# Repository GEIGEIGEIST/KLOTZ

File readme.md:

<picture>
  <source media="(prefers-color-scheme: dark)" srcset="/docs/images/KLOTZ_font_dark.svg">
  <source media="(prefers-color-scheme: light)" srcset="/docs/images/KLOTZ_font_bright.svg">
  
</picture>

# KLOTZ SPLIT KEYBOARD

KLOTZ is a 34 key column-staggered choc split keyboard running [ZMK](https://zmk.dev/). It supports a low profile encoder, three status LEDs on every side and the SplitKB tenting puck.

## LAYOUT

## PCB

[Here](/PCB/) you can find the KiCad files and Gerbers for the KLOTZ.

## SWITCHPLATE

And [here](/switchplate/) is the switchplate, which you should use, if you plan to use hotswap sockets.

## KNOB

You can use pretty much any knob, which works with EC12 encoder, but [here](/knob/) you can find one, I designed for the KLOTZ.

## BUILD GUIDE

The build guide for the KLOTZ can be found [here](/docs/buildguide.md).

## FIRMWARE

[ZMK config](https://github.com/GEIGEIGEIST/zmk-config-klotz) for the KLOTZ.

## TRAVELCASE

Since a lot of people use the Amazon basics harddrive case (ZH1510147) for the KLOTZ I thought I should put an (affiliate) link in here. 

[US Amazon link](https://www.amazon.com/gp/product/B00F5CKWBA?ie=UTF8&psc=1&linkCode=ll1&tag=ekelhaigitspo-21&linkId=67f8dc497a4f2d7a740d78649fa4cf6d&language=us_EN&ref_=as_li_ss_tl)

[German Amazon link](https://www.amazon.de/gp/product/B00F5CKWBA?ie=UTF8&psc=1&linkCode=ll1&tag=ekelhaigitspo-21&linkId=67f8dc497a4f2d7a740d78649fa4cf6d&language=de_DE&ref_=as_li_ss_tl)

 If you build a KLOTZ I would be pretty happy to see some pictures. And if you want to leave me a tip you can do this [here](https://ko-fi.com/geigeigeist) (but please don't feel pressured)

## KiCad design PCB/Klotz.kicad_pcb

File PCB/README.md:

# KLOTZ PCB

## MANUFACTURING
If you want to get the PCB made you need to upload the **KLOTZ_0-2_gerbers.zip** file to the website of the manufacture ([JLCPCB](https://jlcpcb.com/) for example).

- upload the ZIP
- sometimes the Gerber preview from JLCPCB can't display the PCB, even when the files are fine. In this case use this dimensions: 120.5 mm* 85.5 mm
- PCB Thickness 1.6mm
- 2 layers
- PCB Qty as much as you like. But be aware, that you need 2 PCBs for one keyboard
- PCB Color Black
- No impedance control
- Surface Finish HASL(with lead) if you want the easiest soldering experience or LeadFree HASL.
- Remove Order Number Yes

## CHECK TRACES OR PINOUT

If you only want to check the traces or see what is connected to which pin you can take a look at these graphics.

## TAKE A DEEPER LOOK OR MODIFY 

You can download the project if you need to take a deeper look or modify something. You need the Open Source software [KiCad](https://www.kicad.org/) to open it.

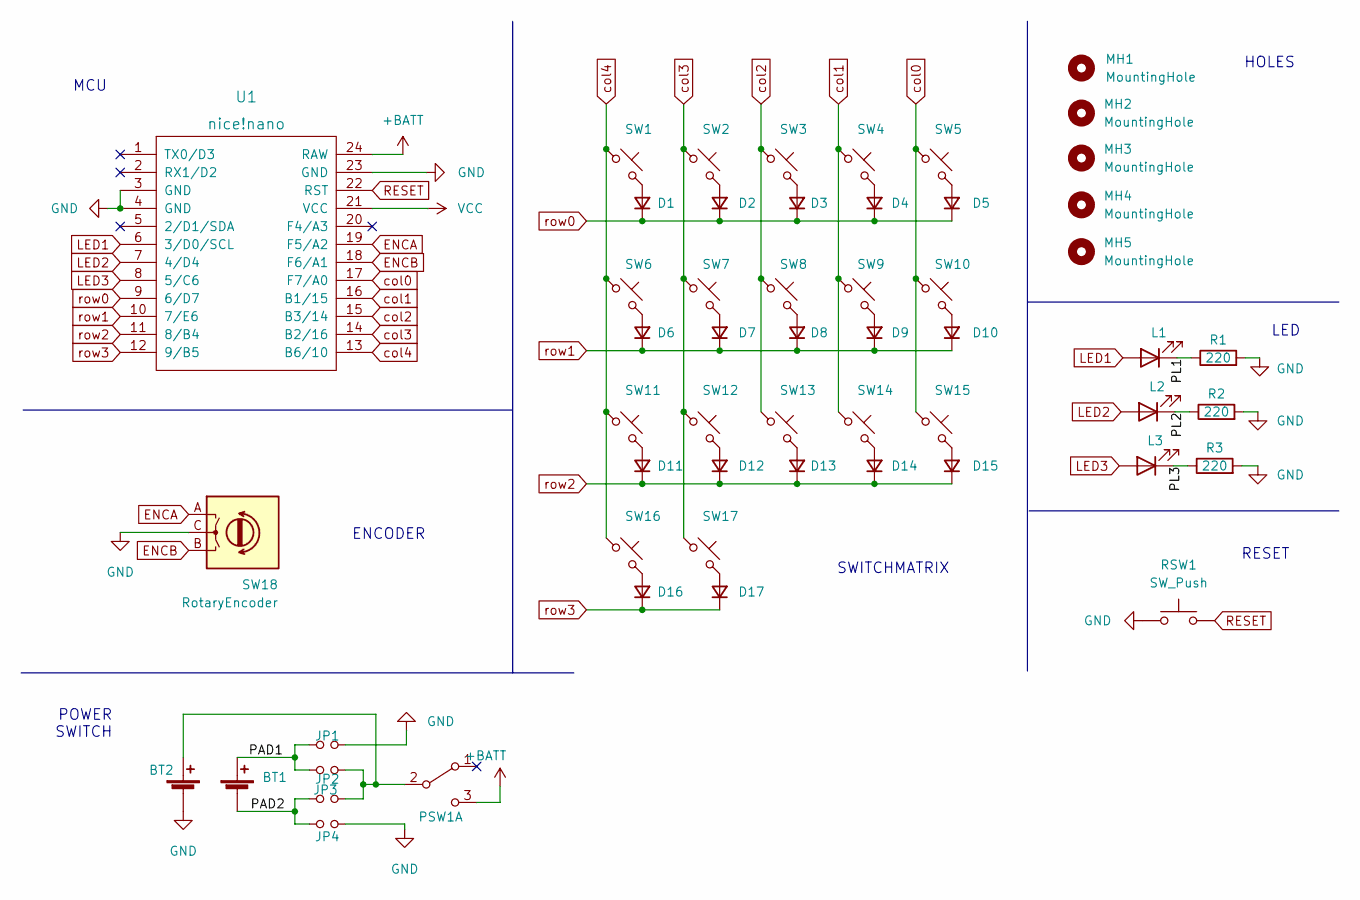
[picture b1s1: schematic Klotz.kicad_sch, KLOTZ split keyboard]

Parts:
BT1: Battery_Cell; JST_PH_reversible
BT2: Battery_Cell; custombatteryconnector
D1, D2, D3, D4, D5, D6, D7, D8, D9, D10, D11, D12, D13, D14, D15, D16, D17: D_Small; Diode_SOD123
JP1, JP2, JP3, JP4: Device_Jumper_NO_Small; Jumper
L1, L2, L3: LED; LED_3mm_reversible
MH1, MH2, MH3, MH4, MH5: MountingHole; MountingHole_2.2mm_M2_ISO7380_Pad
PSW1: SW_DPDT_x2; MSK12C02_reversible
R1, R2, R3: 220; R_1206_DoubleSided
RSW1: SW_Push
SW1, SW2, SW3, SW4, SW5, SW6, SW7, SW8, SW9, SW10, SW11, SW12, SW13, SW14, SW15, SW16, SW17: MX_SW_HS; Kailh_socket_PG1350_optional_reversible
SW18: RotaryEncoder; RotaryEncoder_Alps_EC12E_Vertical_H20mm
U1: nice!nano; ProMicro_v2

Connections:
+BATT: PSW1.3 (C), U1.24 (RAW)
/PAD1: BT1.1 (+), JP1.1, JP2.1
/PAD2: BT1.2 (-), JP3.1, JP4.1
/PL1: L1.1 (K), R1.1
/PL2: L2.1 (K), R2.1
/PL3: L3.1 (K), R3.1
ENCA: SW18.A, U1.19 (F5/A2)
ENCB: SW18.B, U1.18 (F6/A1)
GND: BT2.2 (-), JP1.2, JP4.2, R1.2, R2.2, R3.2, RSW1.1, SW18.C, U1.3 (GND), U1.4 (GND), U1.23 (GND)
LED1: L1.2 (A), U1.6 (3/D0/SCL)
LED2: L2.2 (A), U1.7 (4/D4)
LED3: L3.2 (A), U1.8 (5/C6)
unnamed: BT2.1 (+), JP2.2, JP3.2, PSW1.2 (B)
unnamed: D1.2 (A), SW1.2
unnamed: D2.2 (A), SW2.2
unnamed: D3.2 (A), SW3.2
unnamed: D4.2 (A), SW4.2
unnamed: D5.2 (A), SW5.2
unnamed: D6.2 (A), SW6.2
unnamed: D7.2 (A), SW7.2
unnamed: D8.2 (A), SW8.2
unnamed: D9.2 (A), SW9.2
unnamed: D10.2 (A), SW10.2
unnamed: D11.2 (A), SW11.2
unnamed: D12.2 (A), SW12.2
unnamed: D13.2 (A), SW13.2
unnamed: D14.2 (A), SW14.2
unnamed: D15.2 (A), SW15.2
unnamed: D16.2 (A), SW16.2
unnamed: D17.2 (A), SW17.2
RESET: RSW1.2, U1.22 (RST)
VCC: U1.21 (VCC)
col0: SW5.1, SW10.1, SW15.1, U1.17 (F7/A0)
col1: SW4.1, SW9.1, SW14.1, U1.16 (B1/15)
col2: SW3.1, SW8.1, SW13.1, U1.15 (B3/14)
col3: SW2.1, SW7.1, SW12.1, SW17.1, U1.14 (B2/16)
col4: SW1.1, SW6.1, SW11.1, SW16.1, U1.13 (B6/10)
row0: D1.1 (K), D2.1 (K), D3.1 (K), D4.1 (K), D5.1 (K), U1.9 (6/D7)
row1: D6.1 (K), D7.1 (K), D8.1 (K), D9.1 (K), D10.1 (K), U1.10 (7/E6)
row2: D11.1 (K), D12.1 (K), D13.1 (K), D14.1 (K), D15.1 (K), U1.11 (8/B4)
row3: D16.1 (K), D17.1 (K), U1.12 (9/B5)

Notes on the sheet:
SWITCHMATRIX
POWER SWITCH
HOLES
LED
MCU
RESET
ENCODER

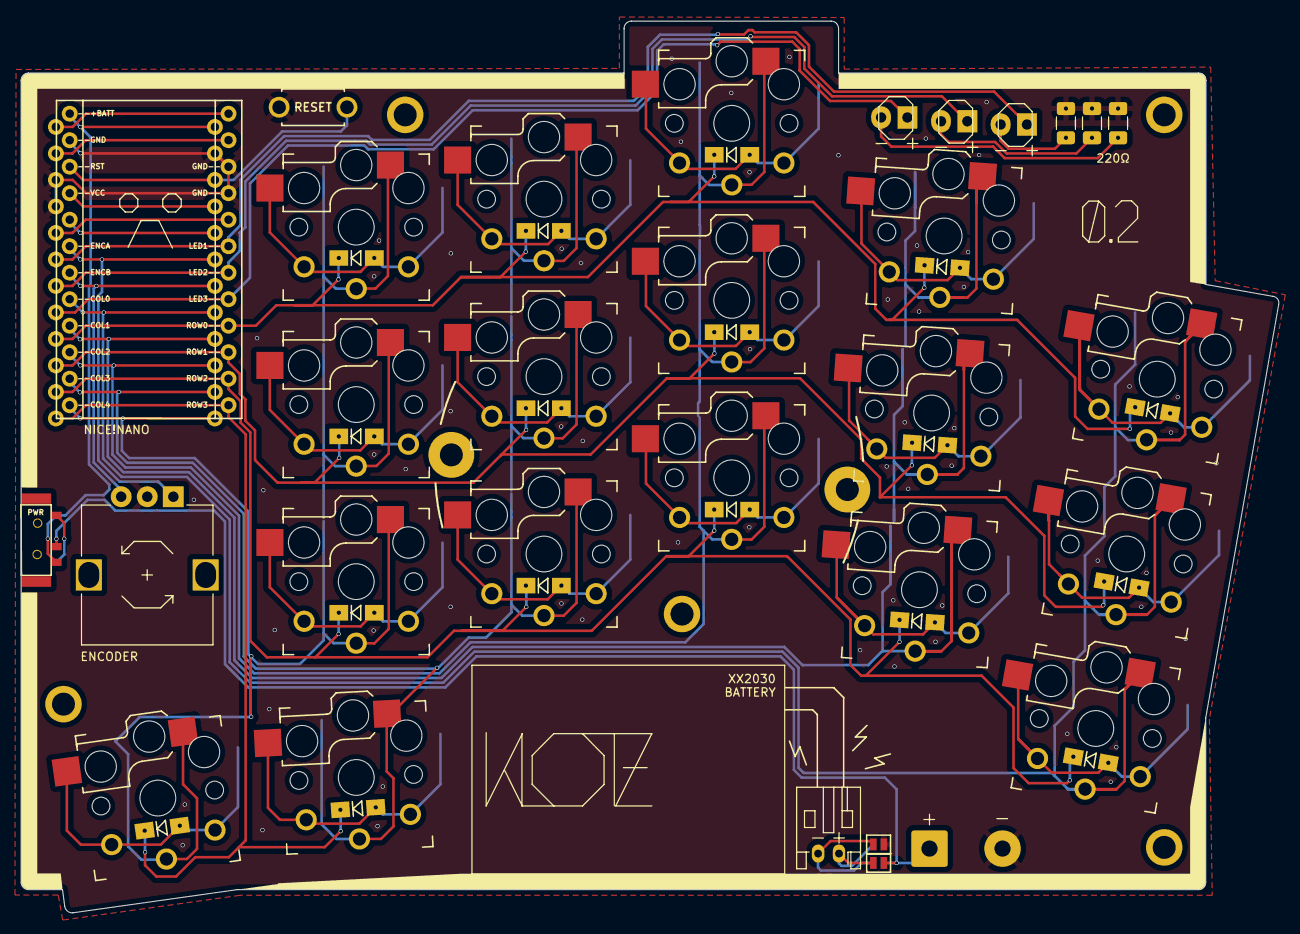
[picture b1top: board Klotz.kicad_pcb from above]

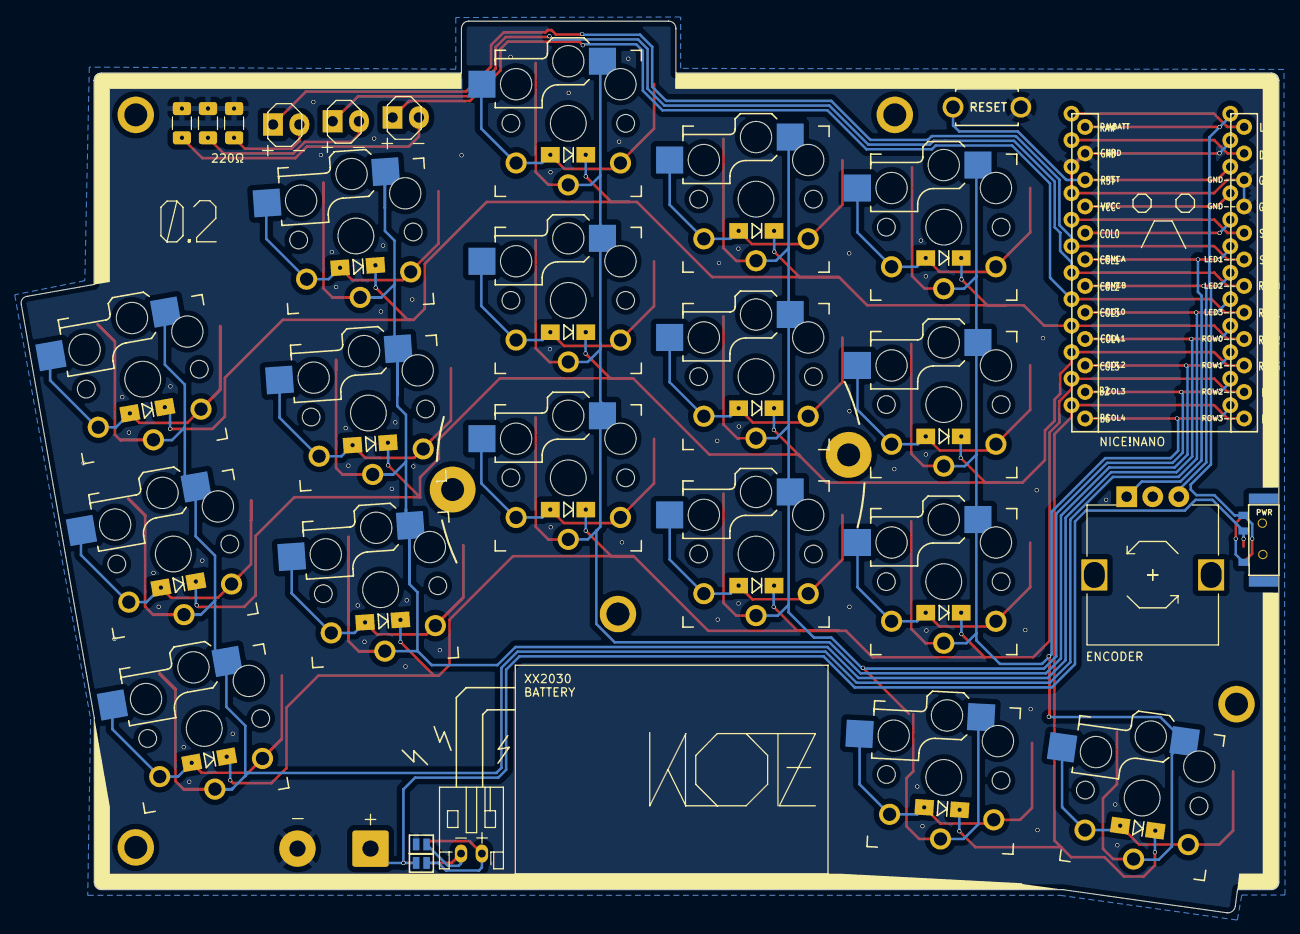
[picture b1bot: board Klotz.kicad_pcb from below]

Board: 2 copper layers, 120.5 x 85.5 mm, 55 parts (3 on the bottom side), 40 nets.

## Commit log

2022-07-02 KLOTZ init
2022-07-02 upload PCB
2022-07-02 add plate files
2022-07-03 add knob
2022-07-03 update KiCad files
2022-07-03 update PCB readme
2022-07-03 update buildguide
2022-07-03 update images
2022-07-03 update bom
2022-07-04 add photos
2022-08-14 update knob
